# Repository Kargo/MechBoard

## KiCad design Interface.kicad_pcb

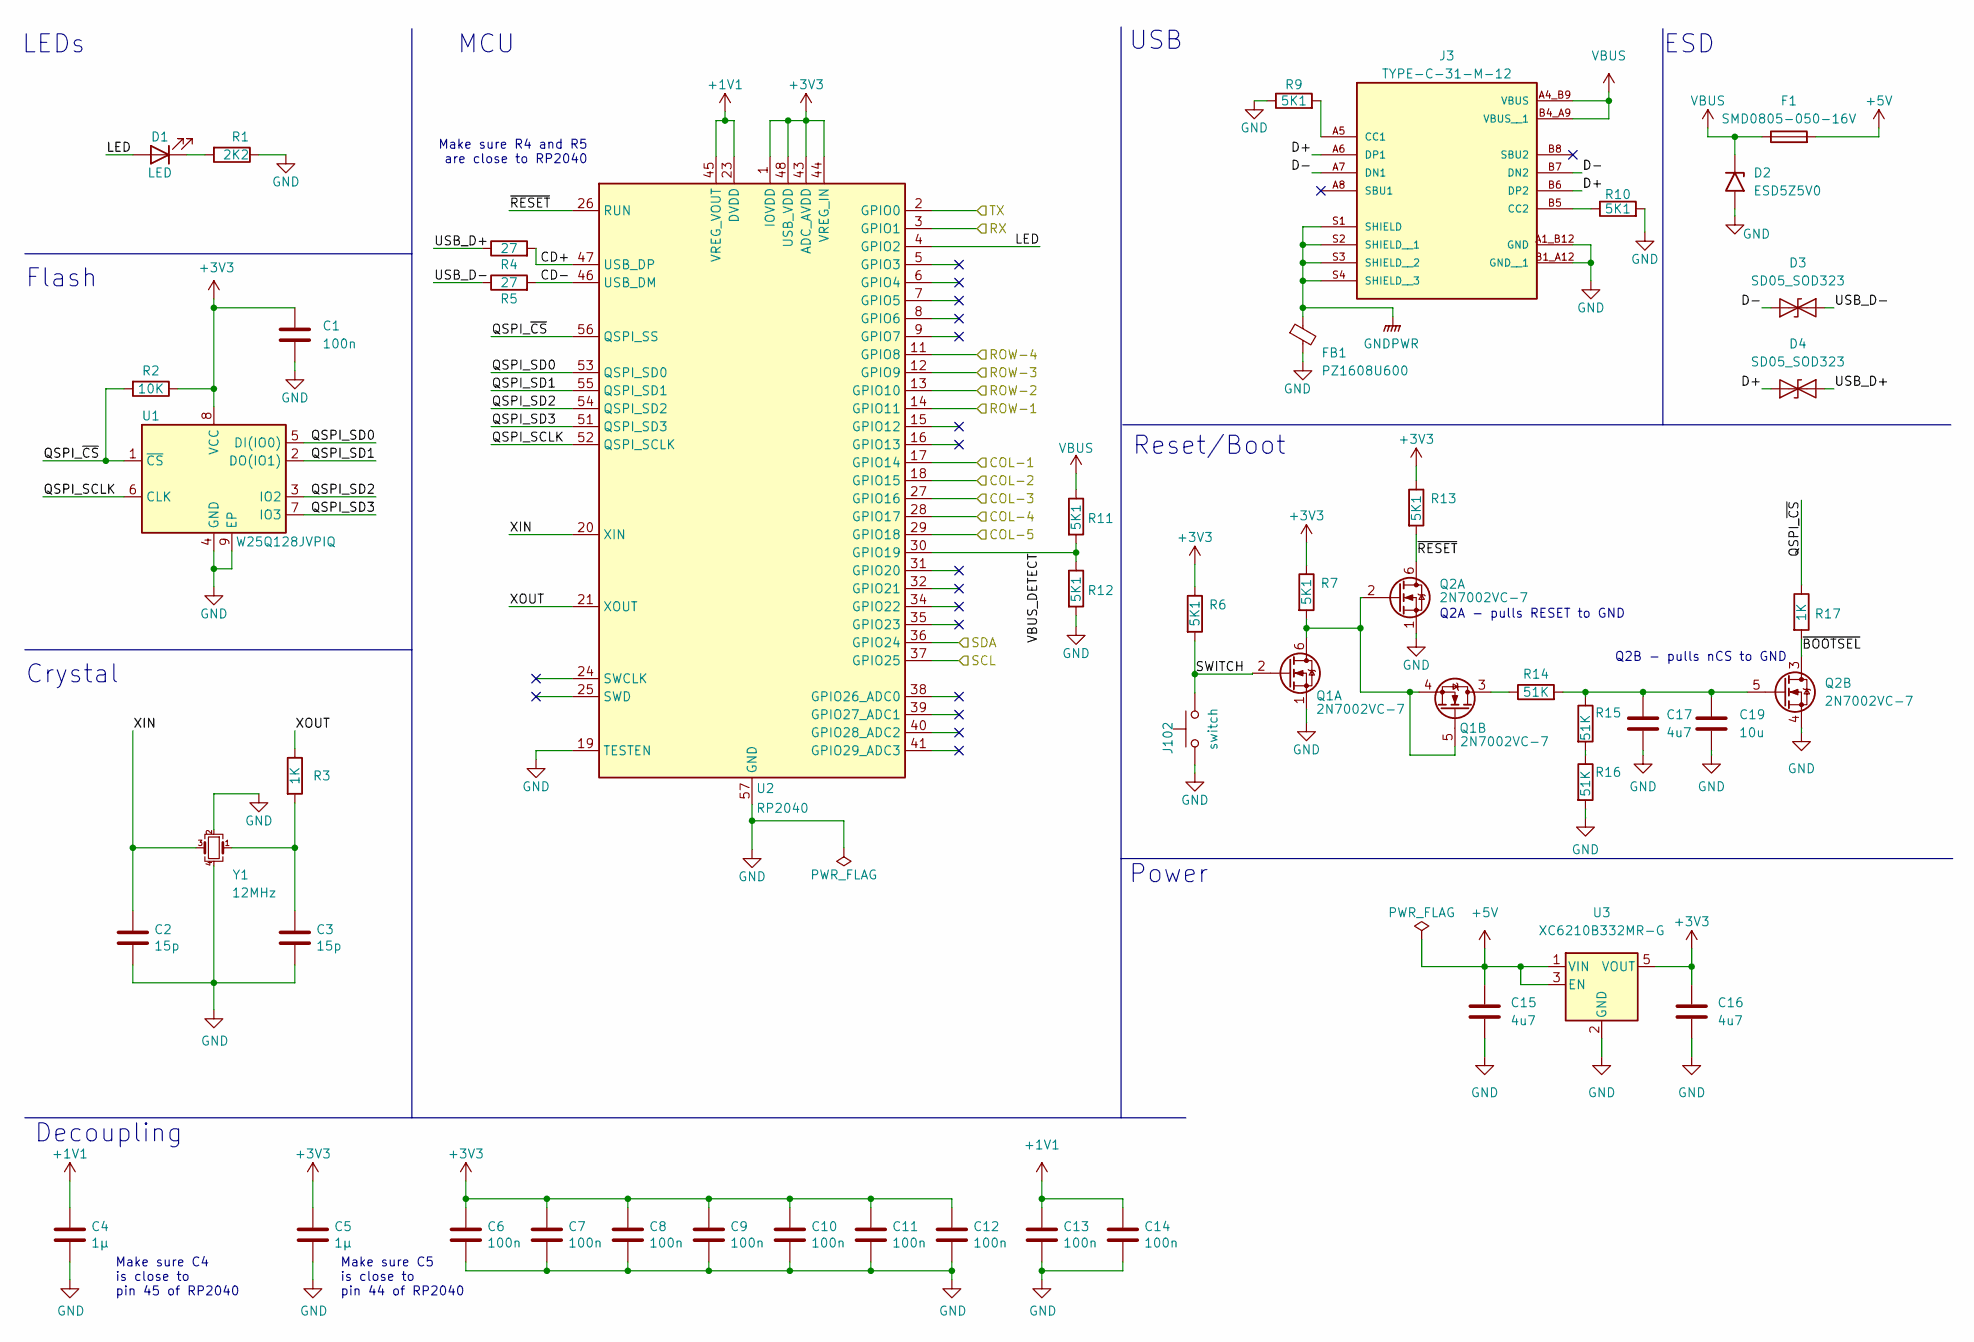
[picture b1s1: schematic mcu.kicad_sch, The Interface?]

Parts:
C1, C6, C7, C8, C9, C10, C11, C12, C13, C14: 100n; C_0402_1005Metric; LCSC C1525
C2, C3: 15p; C_0402_1005Metric
C4, C5: 1µ; C_0402_1005Metric; LCSC C52923
C15, C16: 4u7; C_0603_1608Metric; LCSC C19666
C17: 4u7; C_0402_1005Metric; MPN CL05A475MP5NRNC; JLC Basic Y
C19: 10u; C_0402_1005Metric; MPN CL05A106MQ5NUNC; JLC Basic Y
D1: LED; LED_0603_1608Metric; LCSC C2290
D2: ESD5Z5V0; D_SOD-523; Manufacturer Part Number ESD5Z5V0; LCSC C502546
D3, D4: SD05_SOD323; D_SOD-323; LCSC C2983254
F1: SMD0805-050-16V; Fuse_0805_2012Metric; Manufacturer Part Number SMD0805-050-16V; LCSC C2833485
FB1: PZ1608U600; L_0603_1608Metric; LCSC C98288
J3: TYPE-C-31-M-12; MOLEX_2169900003; Manufacturer Part Number TYPE-C-31-M-12; LCSC C165948
J102: switch; SW_SKHLLCA010; LCSC C115343
Q1, Q2: 2N7002VC-7; SOT-563; MPN 2N7002V; LCSC C504145
R1: 2K2; R_0402_1005Metric
R2: 10K; R_0402_1005Metric
R3: 1K; R_0402_1005Metric
R4, R5: 27; R_0402_1005Metric
R6, R7, R13: 5K1; R_0402_1005Metric; MPN 0402WGF5101TCE; LCSC C25905
R9, R10, R11, R12: 5K1; R_0402_1005Metric
R14, R15, R16: 51K; R_0402_1005Metric; MPN 0402WGF5102TCE; JLC Basic Y
R17: 1K; R_0402_1005Metric; MPN 0402WGF1001TCE; LCSC C11702
U1: W25Q128JVPIQ; WSON_128JVPIQ_WIN
U2: RP2040; QFN-56-1EP_7x7mm_P0.4mm_EP3.2x3.2mm
U3: XC6210B332MR-G; SOT-23-5; LCSC C47719
Y1: 12MHz; Crystal_SMD_2520-4Pin_2.5x2.0mm; LCSC C2149204

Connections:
+1V1: C4.1, C13.1, C14.1, U2.23 (DVDD), U2.45 (VREG_VOUT), U2.50 (DVDD)
+3V3: C1.1, C5.1, C6.1, C7.1, C8.1, C9.1, C10.1, C11.1, C12.1, C16.1, R2.1, R6.1, R7.1, R13.1, U1.8 (VCC), U2.1 (IOVDD), U2.10 (IOVDD), U2.22 (IOVDD), U2.33 (IOVDD), U2.42 (IOVDD), U2.43 (ADC_AVDD), U2.44 (VREG_IN), U2.48 (USB_VDD), U2.49 (IOVDD), U3.5 (VOUT); also elsewhere on the board
+5V: C15.1, F1.2, U3.1 (VIN), U3.3 (EN)
/Left MCU/CD+: R4.2, U2.47 (USB_DP)
/Left MCU/CD-: R5.2, U2.46 (USB_DM)
/Left MCU/COL-1: U2.17 (GPIO14); also elsewhere on the board
/Left MCU/COL-2: U2.18 (GPIO15); also elsewhere on the board
/Left MCU/COL-3: U2.27 (GPIO16); also elsewhere on the board
/Left MCU/COL-4: U2.28 (GPIO17); also elsewhere on the board
/Left MCU/COL-5: U2.29 (GPIO18); also elsewhere on the board
/Left MCU/D+: D4.1 (A1), J3.A6 (DP1), J3.B6 (DP2)
/Left MCU/D-: D3.1 (A1), J3.A7 (DN1), J3.B7 (DN2)
/Left MCU/LED: D1.2 (A), U2.4 (GPIO2)
/Left MCU/QSPI_SCLK: U1.6 (CLK), U2.52 (QSPI_SCLK)
/Left MCU/QSPI_SD0: U1.5 (DI(IO0)), U2.53 (QSPI_SD0)
/Left MCU/QSPI_SD1: U1.2 (DO(IO1)), U2.55 (QSPI_SD1)
/Left MCU/QSPI_SD2: U1.3 (IO2), U2.54 (QSPI_SD2)
/Left MCU/QSPI_SD3: U1.7 (IO3), U2.51 (QSPI_SD3)
/Left MCU/QSPI_~CS: R2.2, R17.1, U1.1 (~CS), U2.56 (QSPI_SS)
/Left MCU/ROW-1: U2.14 (GPIO11); also elsewhere on the board
/Left MCU/ROW-2: U2.13 (GPIO10); also elsewhere on the board
/Left MCU/ROW-3: U2.12 (GPIO9); also elsewhere on the board
/Left MCU/ROW-4: U2.11 (GPIO8); also elsewhere on the board
/Left MCU/RX: U2.3 (GPIO1); also elsewhere on the board
/Left MCU/SCL: U2.37 (GPIO25); also elsewhere on the board
/Left MCU/SDA: U2.36 (GPIO24); also elsewhere on the board
/Left MCU/SWITCH: J102.1, Q1.2 (G), R6.2
/Left MCU/TX: U2.2 (GPIO0); also elsewhere on the board
/Left MCU/USB_D+: D4.2 (A2), R4.1
/Left MCU/USB_D-: D3.2 (A2), R5.1
/Left MCU/VBUS_DETECT: R11.2, R12.1, U2.30 (GPIO19)
/Left MCU/XIN: C2.1, U2.20 (XIN), Y1.3
/Left MCU/XOUT: R3.1, U2.21 (XOUT)
/Left MCU/~BOOTSEL: Q2.3 (D), R17.2
/Left MCU/~RESET: Q2.6 (D), R13.2, U2.26 (RUN)
GND: C1.2, C2.2, C3.2, C4.2, C5.2, C6.2, C7.2, C8.2, C9.2, C10.2, C11.2, C12.2, C13.2, C14.2, C15.2, C16.2, C17.2, C19.2, D2.2 (A2), FB1.2, J3.A1_B12 (GND), J3.B1_A12 (GND__1), J102.2, Q1.1 (S), Q2.1 (S), Q2.4 (S), R1.1, R9.1, R10.2, R12.2, R16.2, U1.4 (GND), U1.9 (EP), U2.19 (TESTEN), U2.57 (GND), U3.2 (GND), Y1.2, Y1.4; also elsewhere on the board
GNDPWR: FB1.1, J3.S1 (SHIELD), J3.S2 (SHIELD__1), J3.S3 (SHIELD__2), J3.S4 (SHIELD__3)
unnamed: C3.1, R3.2, Y1.1
unnamed: D1.1 (K), R1.2
unnamed: J3.A5 (CC1), R9.2
unnamed: J3.B5 (CC2), R10.1
unnamed: Q1.4 (S), Q1.5 (G), Q1.6 (D), Q2.2 (G), R7.2
unnamed: Q1.3 (D), R14.1
unnamed: C17.1, C19.1, Q2.5 (G), R14.2, R15.1
unnamed: R15.2, R16.1
VBUS: D2.1 (A1), F1.1, J3.A4_B9 (VBUS), J3.B4_A9 (VBUS__1), R11.1

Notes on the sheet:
LEDs
Make sure C5 is close to pin 44 of RP2040
ESD
Q2A - pulls RESET to GND
Q2B - pulls nCS to GND
MCU
Power
Make sure C4 is close to pin 45 of RP2040
Decoupling
USB
Crystal
Flash
Reset/Boot
Make sure R4 and R5 are close to RP2040

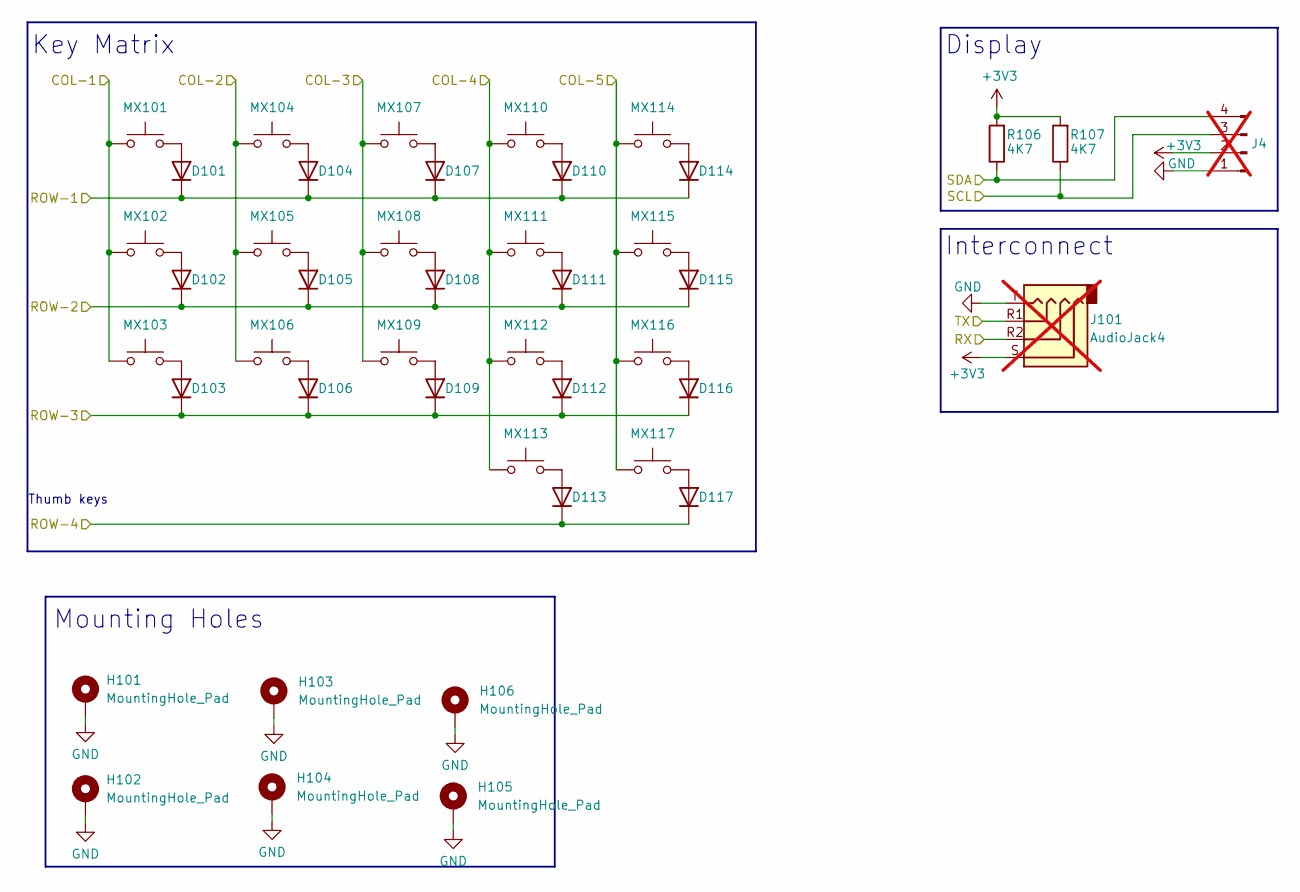
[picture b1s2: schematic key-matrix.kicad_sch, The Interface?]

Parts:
D101, D102, D103, D104, D105, D106, D107, D108, D109, D110, D111, D112, D113, D114, D115, D116, D117: type="D" model="DIODE" lib=""; D_SOD-123
H101, H102, H103, H104, H105, H106: MountingHole_Pad; MountingHole_2.2mm_M2_Pad
J4: CONN_DISPLAY; SSD1306_0.96_Oled; not fitted
J101: AudioJack4; TRRS-PJ-320A; not fitted
MX101, MX102, MX103, MX104, MX105, MX106, MX107, MX108, MX109, MX110, MX111, MX112, MX113, MX114, MX115, MX116, MX117: SW_Push; Kailh_socket_MX
R106, R107: 4K7; R_0402_1005Metric

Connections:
+3V3: J4.2, J101.S, R106.2, R107.2; also elsewhere on the board
/Left MCU/COL-1: MX101.1, MX102.1, MX103.1; also elsewhere on the board
/Left MCU/COL-2: MX104.1, MX105.1, MX106.1; also elsewhere on the board
/Left MCU/COL-3: MX107.1, MX108.1, MX109.1; also elsewhere on the board
/Left MCU/COL-4: MX110.1, MX111.1, MX112.1, MX113.1; also elsewhere on the board
/Left MCU/COL-5: MX114.1, MX115.1, MX116.1, MX117.1; also elsewhere on the board
/Left MCU/ROW-1: D101.1 (K), D104.1 (K), D107.1 (K), D110.1 (K), D114.1 (K); also elsewhere on the board
/Left MCU/ROW-2: D102.1 (K), D105.1 (K), D108.1 (K), D111.1 (K), D115.1 (K); also elsewhere on the board
/Left MCU/ROW-3: D103.1 (K), D106.1 (K), D109.1 (K), D112.1 (K), D116.1 (K); also elsewhere on the board
/Left MCU/ROW-4: D113.1 (K), D117.1 (K); also elsewhere on the board
/Left MCU/RX: J101.R2; also elsewhere on the board
/Left MCU/SCL: J4.3, R107.1; also elsewhere on the board
/Left MCU/SDA: J4.4, R106.1; also elsewhere on the board
/Left MCU/TX: J101.R1; also elsewhere on the board
GND: H101.1, H102.1, H103.1, H104.1, H105.1, H106.1, J4.1, J101.T; also elsewhere on the board
unnamed: D101.2 (A), MX101.2
unnamed: D102.2 (A), MX102.2
unnamed: D103.2 (A), MX103.2
unnamed: D104.2 (A), MX104.2
unnamed: D105.2 (A), MX105.2
unnamed: D106.2 (A), MX106.2
unnamed: D107.2 (A), MX107.2
unnamed: D108.2 (A), MX108.2
unnamed: D109.2 (A), MX109.2
unnamed: D110.2 (A), MX110.2
unnamed: D111.2 (A), MX111.2
unnamed: D112.2 (A), MX112.2
unnamed: D113.2 (A), MX113.2
unnamed: D114.2 (A), MX114.2
unnamed: D115.2 (A), MX115.2
unnamed: D116.2 (A), MX116.2
unnamed: D117.2 (A), MX117.2

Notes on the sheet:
Display
Thumb keys
Mounting Holes
Key Matrix
Interconnect

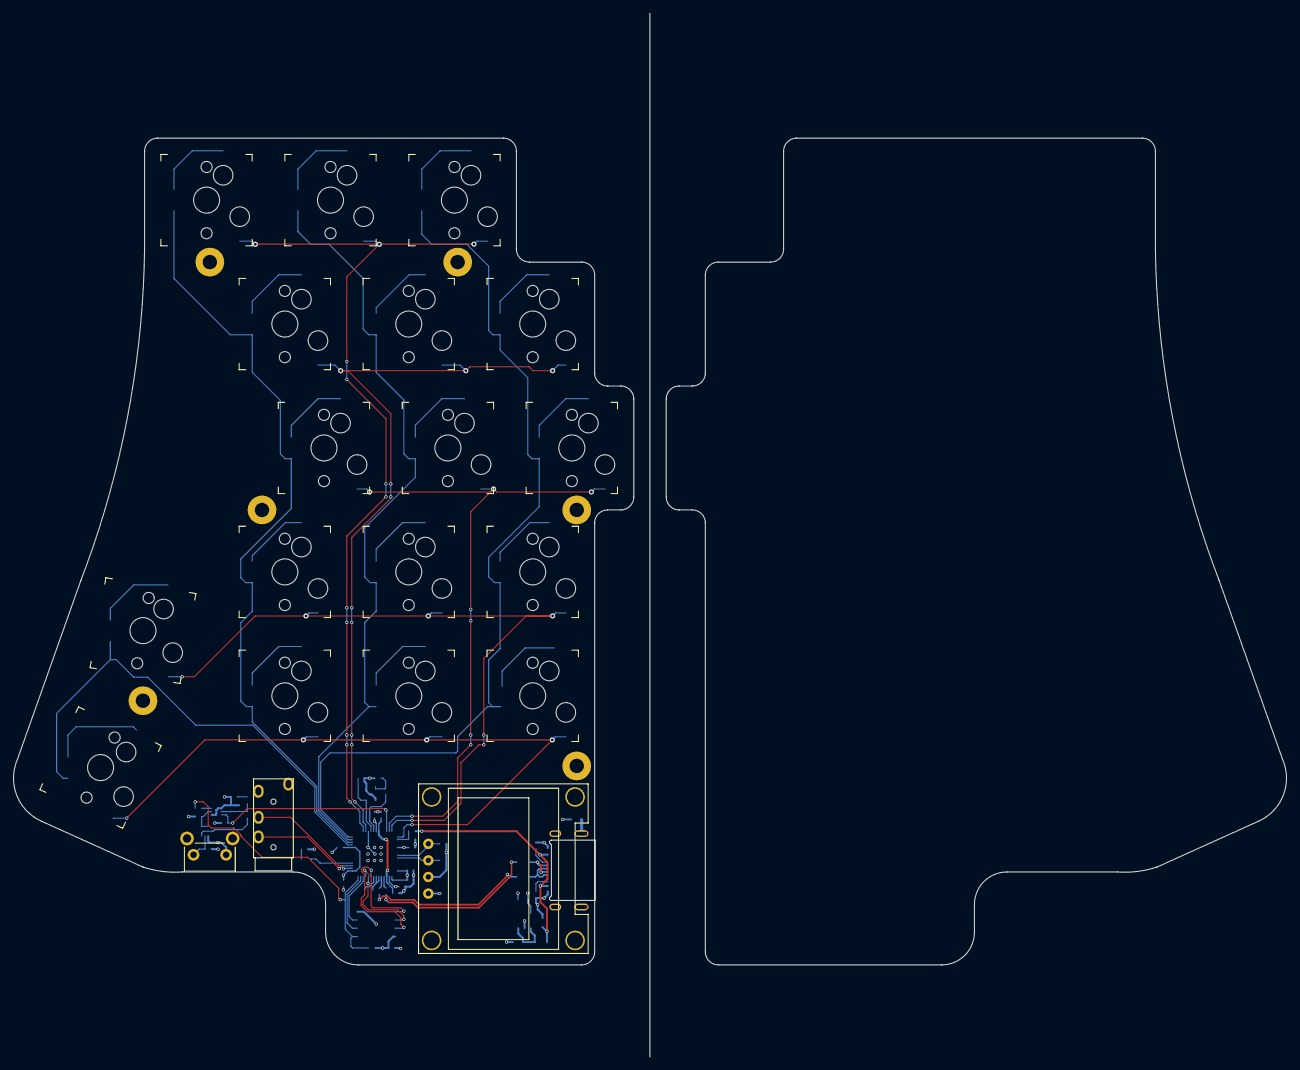
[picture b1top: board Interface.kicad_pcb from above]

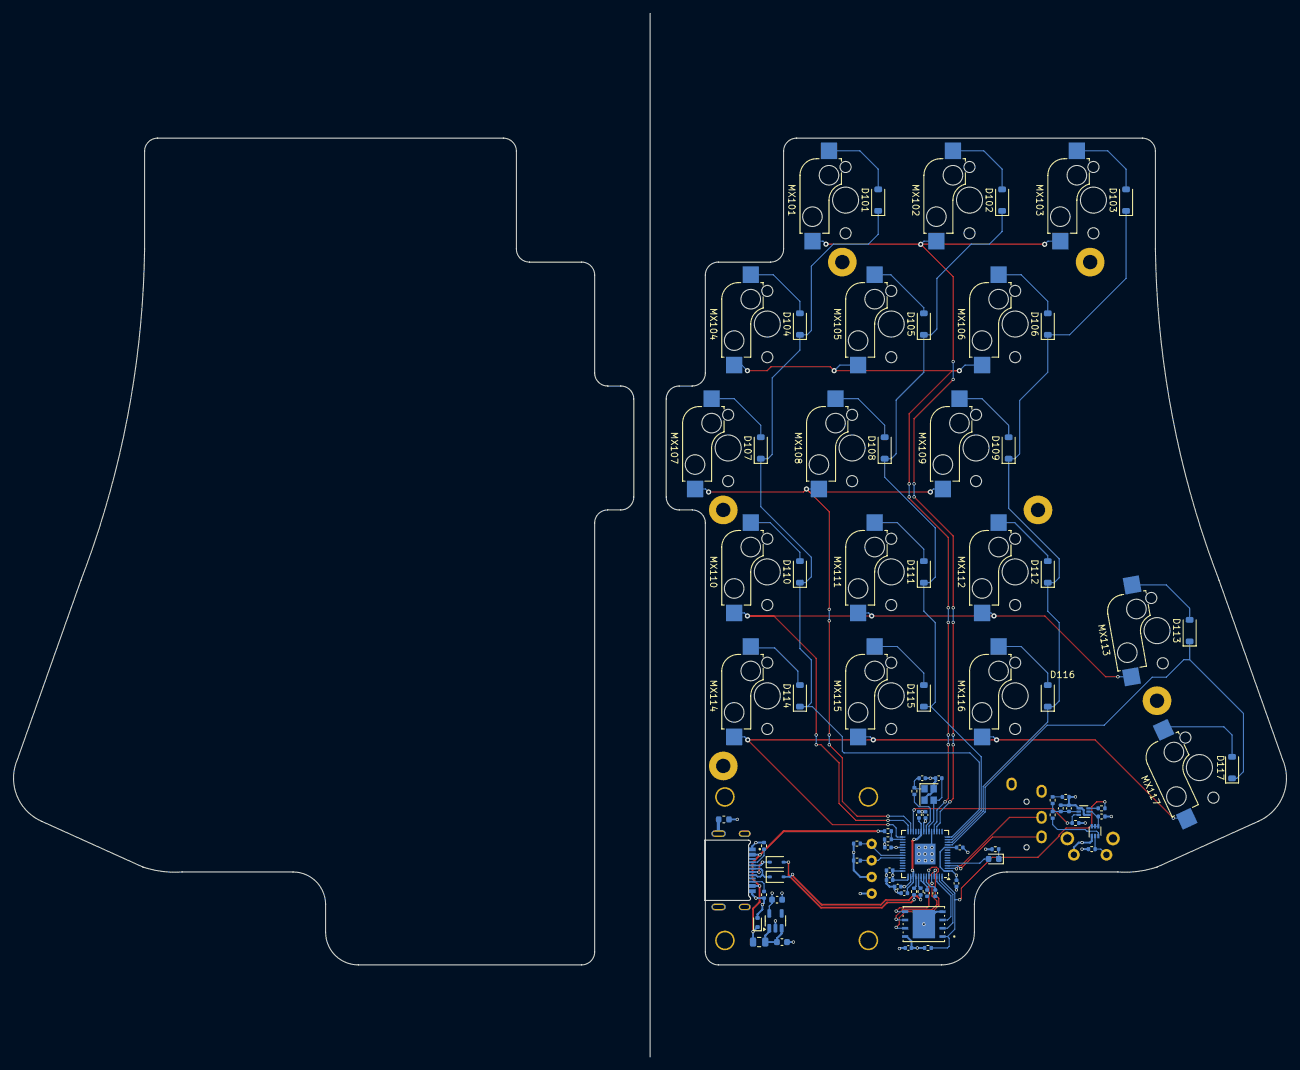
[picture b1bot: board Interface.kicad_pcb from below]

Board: 4 copper layers, 195.2 x 160.0 mm, 92 parts (66 on the bottom side), 63 nets.

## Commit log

2024-01-15 Add mounting holes
2024-02-03 remove backups
2024-03-04 Cleanup routing
2024-03-04 Fix zones
2024-03-04 add GND vias
2024-03-05 Update footprints
2024-03-16 align schematic to grid
2024-03-16 Complete routing
2024-05-15 Rotate and add mirror line
